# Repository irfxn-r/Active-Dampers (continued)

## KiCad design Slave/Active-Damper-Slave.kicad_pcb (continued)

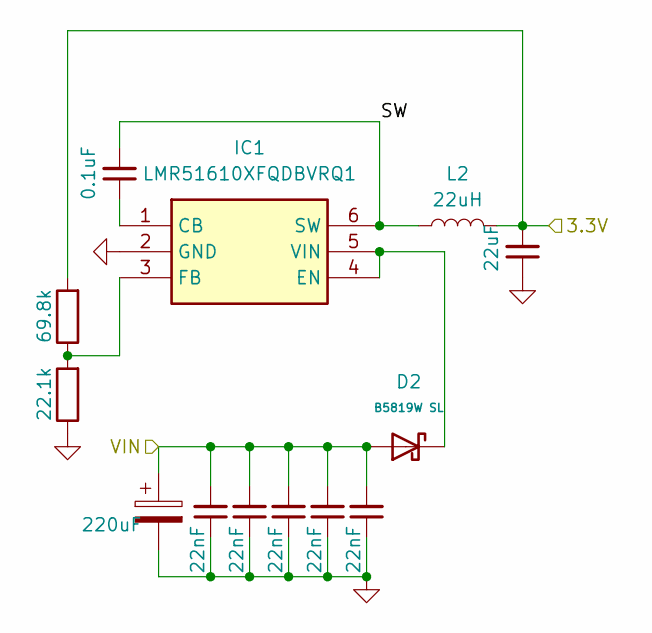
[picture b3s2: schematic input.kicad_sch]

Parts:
C21: 220uF; CP_Radial_D8.0mm_P3.50mm
C23, C32, C33, C34, C35: 22nF; C_0603_1608Metric; Manufacturer_Part_Number CL05A106MP5NUNC; LCSC C21122
C41: 0.1uF; C_0603_1608Metric; Manufacturer_Part_Number CL05A106MP5NUNC; LCSC C21122
C42: 22uF; C_0603_1608Metric; Manufacturer_Part_Number CL05A106MP5NUNC; LCSC C21122
D2: B5819W SL; D_SOD-123; Forward Voltage (Vf@If) 600mV@1A; Reverse Voltage (Vr) 40V; Part B5819W SL; LCSC C8598
IC1: LMR51610XFQDBVRQ1; SOT95P280X145-6N; Mouser Part Number 595-LMR51610XFQDBRQ1
L2: 22uH; L_Taiyo-Yuden_MD-4040
R8: 69.8k; R_0603_1608Metric; Manufacturer_Part_Number RC0402FR-071KL; LCSC C23186
R9: 22.1k; R_0603_1608Metric; Manufacturer_Part_Number RC0402FR-071KL; LCSC C23186

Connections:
+3.3V: C42.2, L2.2, R8.2; also elsewhere on the board
+12V: C21.1, C23.2, C32.2, C33.2, C34.2, C35.2, D2.2; also elsewhere on the board
/Input Filtering/SW: C41.2, IC1.6 (SW), L2.1
GND: C21.2, C23.1, C32.1, C33.1, C34.1, C35.1, C42.1, IC1.2 (GND), R9.1; also elsewhere on the board
unnamed: C41.1, IC1.1 (CB)
unnamed: D2.1, IC1.4 (EN), IC1.5 (VIN)
unnamed: IC1.3 (FB), R8.1, R9.2

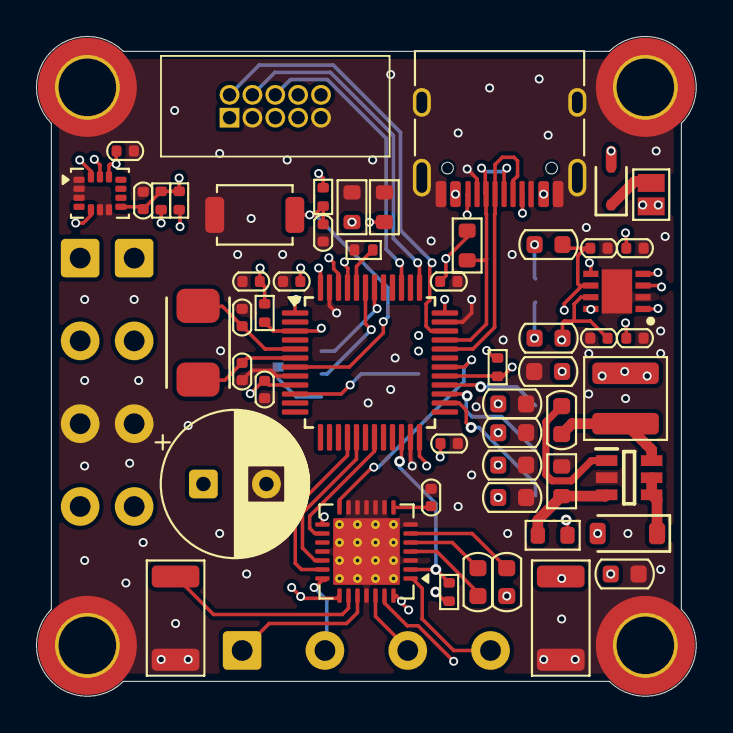
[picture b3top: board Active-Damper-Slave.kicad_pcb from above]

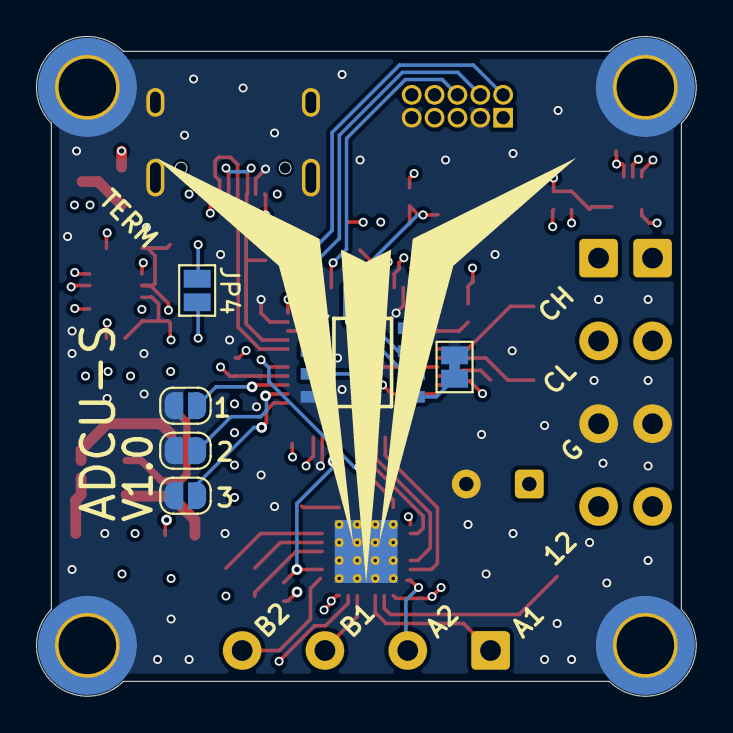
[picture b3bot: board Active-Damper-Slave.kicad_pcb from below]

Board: 4 copper layers, 36.7 x 36.7 mm, 67 parts (6 on the bottom side), 50 nets.

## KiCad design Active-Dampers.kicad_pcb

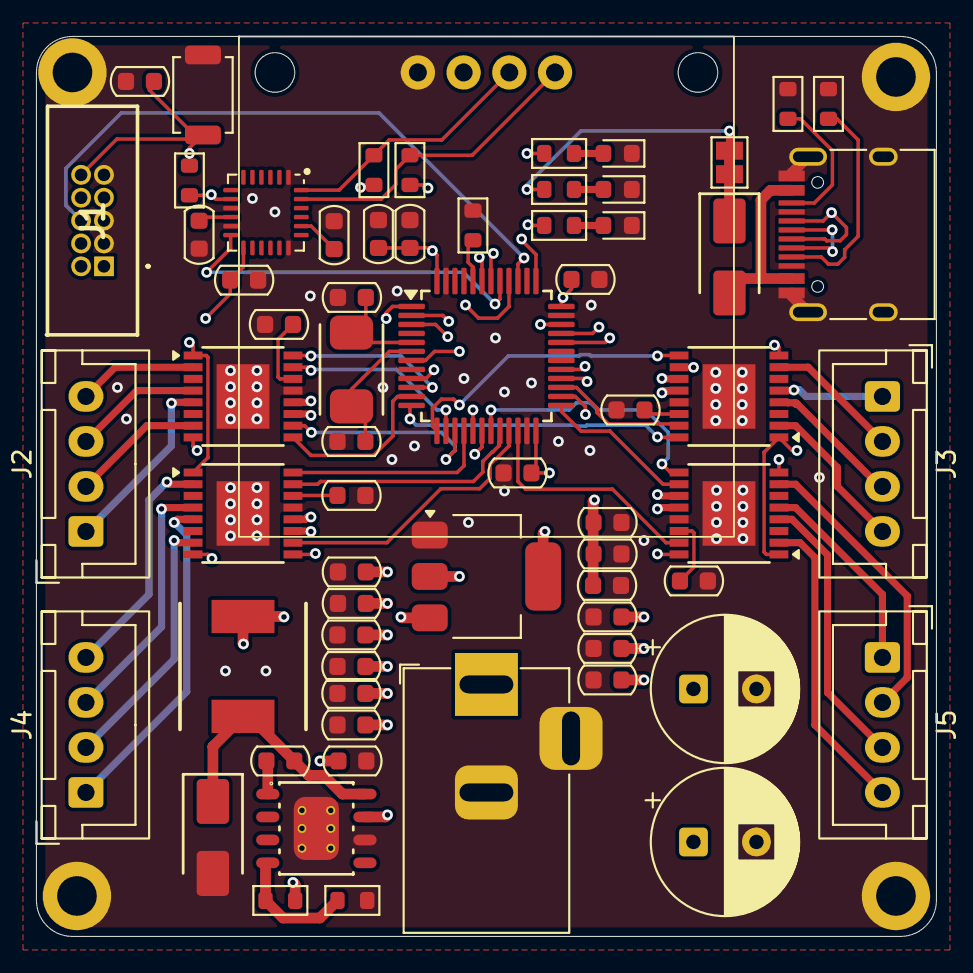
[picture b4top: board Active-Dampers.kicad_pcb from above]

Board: 4 copper layers, 50.0 x 50.0 mm, 70 parts (0 on the bottom side), 69 nets.

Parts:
C1, C6, C26: 100nF; C_0603_1608Metric
C2, C3: 22pF; C_0603_1608Metric
C5, C8, C9: 10uF; C_0603_1608Metric
C7: 1uF; C_0603_1608Metric
C10: 2.2nF; C_0603_1608Metric
C11, C12, C13, C14: 2.2uF; C_0603_1608Metric
C15, C22: 220uF; CP_Radial_D8.0mm_P3.50mm
C16, C17, C18, C19, C20: 22nF; C_0603_1608Metric
C21: 10nF; C_0603_1608Metric
C23, C24, C25, C27, C28, C29, C30: 22uF; C_0603_1608Metric
C34: 0.1uF; C_0603_1608Metric
D1, D3: SS54; D_SMA
D7, D12, D14: LED BLUE; LED_0603_1608Metric
H1, H2, H3, H4: MountingHole_M3_3.2mm_Pad; MountingHole_2.2mm_M2_ISO14580_Pad
J1: Conn_ARM_JTAG_SWD_10; 62701021621
J2: FL; JST_XH_B4B-XH-A_1x04_P2.50mm_Vertical
J3: FR; JST_XH_B4B-XH-A_1x04_P2.50mm_Vertical
J4: RL; JST_XH_B4B-XH-A_1x04_P2.50mm_Vertical
J5: RR; JST_XH_B4B-XH-A_1x04_P2.50mm_Vertical
J6: Barrel_Jack_Switch_Pin3Ring; BarrelJack_Horizontal
J7: USB_C_Receptacle_USB2.0_16P; USB_C_Receptacle_HRO_TYPE-C-31-M-12
J8: OLED; OLED_0.96
JP2: SolderJumper_2_Bridged; SolderJumper-2_P1.3mm_Bridged_Pad1.0x1.5mm
L1: 15uH; Inductor_7.3x6.6mm
R1: 1k; R_0603_1608Metric
R2, R7: 10k; R_0603_1608Metric
R3, R4: 5k1; R_0603_1608Metric
R5, R16: 4.7k; R_0603_1608Metric
R8: 3.24k; R_0603_1608Metric
R13: 330; R_0603_1608Metric
R28: 680; R_0603_1608Metric
R30: 2k; R_0603_1608Metric
SW1: SW_SPST; SW_SPST_TS-1088-xR025
U1: MPU-6050; QFN-24-1EP_4x4mm_P0.5mm
U2: STM32F103C8T6; LQFP-48_7x7mm_P0.5mm
U6, U7, U8, U9: DRV8848; TSSOP-16-1EP_4.4x5mm_P0.65mm
U10: TPS5430DDAR; ESOP-8_L4.9-W3.9-P1.27-LS6.0-TL-EP
U11: AMS1117-3.3; SOT-223-3_TabPin2
X1: X50328MSB2GI; CRYSTAL-SMD_L5.0-W3.2

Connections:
+3.3V: C5.2, C6.2, C7.2, C8.2, C9.2, C28.2, C29.2, C30.2, J1.1 (VTref), J8.2, R1.1, R5.1, R13.1, R16.1, U1.8 (VLOGIC), U1.13 (VDD), U2.1 (VBAT), U2.9 (VDDA), U2.24 (VDD), U2.36 (VDD), U2.48 (VDD), U6.11 (VREF), U7.11 (VREF), U8.11 (VREF), U9.11 (VREF), U11.2 (VO)
+5V: C22.1, C23.2, C24.2, C25.2, C26.2, C27.2, JP2.2 (B), L1.2, R7.2, R28.1, U11.3 (VI)
+12V: C15.1, C16.2, C17.2, C18.2, C19.2, C20.2, J6.1, R30.1, U6.12 (VM), U7.12 (VM), U8.12 (VM), U9.12 (VM), U10.7 (VIN)
/AIN1_FL: U2.10 (PA0), U6.16 (AIN1)
/AIN1_FR: U2.12 (PA2), U7.16 (AIN1)
/AIN1_RL: U2.16 (PA6), U8.16 (AIN1)
/AIN1_RR: U2.18 (PB0), U9.16 (AIN1)
/AIN2_FL: U2.14 (PA4), U6.15 (AIN2)
/AIN2_FR: U2.27 (PB14), U7.15 (AIN2)
/AIN2_RL: U2.20 (PB2), U8.15 (AIN2)
/AIN2_RR: U2.22 (PB11), U9.15 (AIN2)
/AOUT1_FL: J2.4, U6.2 (AOUT1)
/AOUT1_FR: J3.4, U7.2 (AOUT1)
/AOUT1_RL: J4.4, U8.2 (AOUT1)
/AOUT1_RR: J5.4, U9.2 (AOUT1)
/AOUT2_FL: J2.3, U6.4 (AOUT2)
/AOUT2_FR: J3.3, U7.4 (AOUT2)
/AOUT2_RL: J4.3, U8.4 (AOUT2)
/AOUT2_RR: J5.3, U9.4 (AOUT2)
/BIN1_FL: U2.11 (PA1), U6.9 (BIN1)
/BIN1_FR: U2.13 (PA3), U7.9 (BIN1)
/BIN1_RL: U2.17 (PA7), U8.9 (BIN1)
/BIN1_RR: U2.19 (PB1), U9.9 (BIN1)
/BIN2_FL: U2.15 (PA5), U6.10 (BIN2)
/BIN2_FR: U2.26 (PB13), U7.10 (BIN2)
/BIN2_RL: U2.21 (PB10), U8.10 (BIN2)
/BIN2_RR: U2.25 (PB12), U9.10 (BIN2)
/BOUT1_FL: J2.2, U6.7 (BOUT1)
/BOUT1_FR: J3.2, U7.7 (BOUT1)
/BOUT1_RL: J4.2, U8.7 (BOUT1)
/BOUT1_RR: J5.2, U9.7 (BOUT1)
/BOUT2_FL: J2.1, U6.5 (BOUT2)
/BOUT2_FR: J3.1, U7.5 (BOUT2)
/BOUT2_RL: J4.1, U8.5 (BOUT2)
/BOUT2_RR: J5.1, U9.5 (BOUT2)
/IMU_INT: U1.12 (INT), U2.41 (PB5)
/SCL: J8.4, R5.2, U1.23 (SCL), U2.42 (PB6)
/SDA: J8.3, R16.2, U1.24 (SDA), U2.43 (PB7)
/SWCLK/TCK: J1.4 (SWCLK/TCK), U2.37 (PA14)
/SWDIO/TMS: J1.2 (SWDIO/TMS), U2.34 (PA13)
/SWO/TDO: J1.6 (SWO/TDO), U2.39 (PB3)
/USB+: J7.A6 (D+), J7.B6 (D+), U2.33 (PA12)
/USB-: J7.A7 (D-), J7.B7 (D-), U2.32 (PA11)
/~FAULT_FL: U2.2 (PC13), U6.8 (~FAULT)
/~FAULT_FR: U2.29 (PA8), U7.8 (~FAULT)
/~FAULT_RL: U2.3 (PC14), U8.8 (~FAULT)
/~FAULT_RR: U2.28 (PB15), U9.8 (~FAULT)
/~SLEEP: U2.40 (PB4), U6.1 (~SLEEP), U7.1 (~SLEEP), U8.1 (~SLEEP), U9.1 (~SLEEP)
GND: C1.1, C2.1, C3.1, C5.1, C6.1, C7.1, C8.1, C9.1, C10.2, C11.1, C12.1, C13.1, C14.1, C15.2, C16.1, C17.1, C18.1, C19.1, C20.1, C22.2, C23.1, C24.1, C25.1, C26.1, C27.1, C28.1, C29.1, C30.1, C34.2, D3.2, D7.1 (K), D12.1 (K), D14.1 (K), H1.1, H2.1, H3.1, H4.1, J1.3 (GND), J1.5 (GND), J1.9 (GNDDetect), J6.2, J6.3, J7.A1 (GND), J7.A8 (SBU1), J7.A12 (GND), J7.B1 (GND), J7.B8 (SBU2), J7.B12 (GND), J7.S1 (SHIELD), J8.1, R2.1, R3.2, R4.2, R8.1, SW1.2 (B), U1.1 (CLKIN), U1.9 (AD0), U1.11 (FSYNC), U1.18 (GND), U2.8 (VSSA), U2.23 (VSS), U2.35 (VSS), U2.47 (VSS), U6.13 (GND), U6.17 (GND), U7.13 (GND), U7.17 (GND), U8.13 (GND), U8.17 (GND), U9.13 (GND), U9.17 (GND), U10.6 (GND), U10.9 (GND_(EP)), U11.1 (GND)
unnamed: D1.2, J7.A4 (VBUS), J7.A9 (VBUS), J7.B4 (VBUS), J7.B9 (VBUS)
unnamed: D7.2 (A), R13.2
unnamed: D12.2 (A), R28.2
unnamed: D14.2 (A), R30.2
unnamed: C1.2, J1.10 (~RESET), R1.2, SW1.1 (A), U2.7 (NRST)
unnamed: J7.A5 (CC1), R3.1
unnamed: J7.B5 (CC2), R4.1
unnamed: D1.1, JP2.1 (A)
unnamed: C10.1, U1.20 (CPOUT)
unnamed: C34.1, U1.10 (REGOUT)
unnamed: R2.2, U2.44 (BOOT0)
unnamed: C2.2, U2.5 (PD0), X1.2
unnamed: C3.2, U2.6 (PD1), X1.1
unnamed: C14.2, U6.14 (VINT)
unnamed: C11.2, U7.14 (VINT)
unnamed: C12.2, U8.14 (VINT)
unnamed: C13.2, U9.14 (VINT)
unnamed: C21.1, U10.1 (BOOT)
unnamed: C21.2, D3.1, L1.1, U10.8 (PH)
unnamed: R7.1, R8.2, U10.4 (VSENSE)

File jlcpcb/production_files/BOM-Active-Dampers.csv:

Comment,Designator,Footprint,LCSC,Quantity
0.1uF,C34,C_0603_1608Metric,C14663,1
100nF,"C1,C26,C6",C_0603_1608Metric,C14663,3
10k,"R2,R7",R_0603_1608Metric,C25804,2
10nF,C21,C_0603_1608Metric,C57112,1
10uF,"C5,C8,C9",C_0603_1608Metric,C96446,3
15uH,L1,Inductor_7.3x6.6mm,C2045384,1
1k,R1,R_0603_1608Metric,C21190,1
1uF,C7,C_0603_1608Metric,C15849,1
2.2nF,C10,C_0603_1608Metric,C1604,1
2.2uF,"C11,C12,C13,C14",C_0603_1608Metric,C23630,4
22nF,"C16,C17,C18,C19,C20",C_0603_1608Metric,C21122,5
22pF,"C2,C3",C_0603_1608Metric,C1653,2
22uF,"C23,C24,C25,C27,C28,C29,C30",C_0603_1608Metric,C59461,7
2k,R30,R_0603_1608Metric,C22975,1
3.24k,R8,R_0603_1608Metric,C22978,1
330,R13,R_0603_1608Metric,C23138,1
4.7k,"R16,R5",R_0603_1608Metric,C23162,2
5k1,"R3,R4",R_0603_1608Metric,C23186,2
680,R28,R_0603_1608Metric,C23228,1
AMS1117-3.3,U11,SOT-223-3_TabPin2,C6186,1
DRV8848,"U6,U7,U8,U9",TSSOP-16-1EP_4.4x5mm_P0.65mm,C131079,4
LED BLUE,"D12,D14,D7",LED_0603_1608Metric,C2286,3
MPU-6050,U1,QFN-24-1EP_4x4mm_P0.5mm,C24112,1
SS54,"D1,D3",D_SMA,C22452,2
STM32F103C8T6,U2,LQFP-48_7x7mm_P0.5mm,C8734,1
SW_SPST,SW1,SW_SPST_TS-1088-xR025,C720477,1
TPS5430DDAR,U10,ESOP-8_L4.9-W3.9-P1.27-LS6.0-TL-EP,C9864,1
USB_C_Receptacle_USB2.0_16P,J7,USB_C_Receptacle_HRO_TYPE-C-31-M-12,C165948,1
X50328MSB2GI,X1,CRYSTAL-SMD_L5.0-W3.2,C115962,1

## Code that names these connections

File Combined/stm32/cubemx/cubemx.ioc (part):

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Mcu.Name=STM32F103C(8-B)Tx
Mcu.Package=LQFP48
Mcu.UserName=STM32F103C8Tx
PA0-WKUP.GPIOParameters=GPIO_Label
PA0-WKUP.GPIO_Label=AIN1_FL
PA0-WKUP.Signal=S_TIM2_CH1_ETR
PA1.GPIOParameters=GPIO_Label
PA1.GPIO_Label=BIN1_FL
PA1.Signal=S_TIM2_CH2
PA10.Mode=Asynchronous
PA10.Signal=USART1_RX
PA11.Mode=Device
PA11.Signal=USB_DM
PA12.Mode=Device
PA12.Signal=USB_DP
PA13.Mode=Trace_Asynchronous_SW
PA13.Signal=SYS_JTMS-SWDIO
PA14.Mode=Trace_Asynchronous_SW
PA14.Signal=SYS_JTCK-SWCLK
PA2.GPIOParameters=GPIO_Label
PA2.GPIO_Label=AIN1_FR
PA2.Signal=S_TIM2_CH3
PA3.GPIOParameters=GPIO_Label
PA3.GPIO_Label=BIN1_FR
PA3.Signal=S_TIM2_CH4
PA4.GPIOParameters=GPIO_Label
PA4.GPIO_Label=AIN2_FL
PA4.Signal=GPIO_Output
PA5.Signal=GPIO_Output
PA6.Signal=S_TIM3_CH1
PA7.Signal=S_TIM3_CH2
PA9.Mode=Asynchronous
PA9.Signal=USART1_TX
PB0.Signal=S_TIM3_CH3
PB1.Signal=S_TIM3_CH4
PB3.Mode=Trace_Asynchronous_SW
PB3.Signal=SYS_JTDO-TRACESWO
PB6.Mode=I2C
PB6.Signal=I2C1_SCL
PB7.Mode=I2C
PB7.Signal=I2C1_SDA
PB8.Mode=CAN_Activate
PB8.Signal=CAN_RX
PB9.Mode=CAN_Activate
PB9.Signal=CAN_TX
PD0-OSC_IN.Mode=HSE-External-Oscillator
PD0-OSC_IN.Signal=RCC_OSC_IN
PD1-OSC_OUT.Mode=HSE-External-Oscillator
PD1-OSC_OUT.Signal=RCC_OSC_OUT
RCC.SYSCLKFreq_VALUE=72000000
RCC.SYSCLKSource=RCC_SYSCLKSOURCE_PLLCLK
board=custom

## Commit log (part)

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2026-01-12 redo design to esp32
2026-01-14 begin layout
2026-01-16 add cubemx project and redo some layour with new parts
2026-01-17 keep working on pcb
2026-01-18 prod
2026-01-19 create prod files
